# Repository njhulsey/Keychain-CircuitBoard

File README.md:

# Keychain-CircuitBoard
As a simple birthday present to my brother, I designed a simple circuit board that fits on your keychain and flashes when you shake it.

WHAT I LEARNED:
- Eagle design
- Vibration Sensor Switch
- OSH Park PCB Ordering

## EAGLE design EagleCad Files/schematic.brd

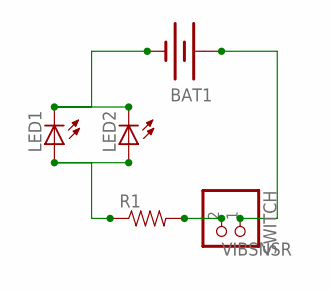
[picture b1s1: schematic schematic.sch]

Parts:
BAT1: BATTERY12PTH; BATTCON_12MM_PTH
LED1, LED2: LED5MM
R1: RESISTORKIT; AXIAL-0.3-KIT
SWITCH: PINHD-1X2; 1X02

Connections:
unnamed: BAT1.GND (-), LED1.K (C), LED2.K (C)
unnamed: LED1.A, LED2.A, R1.P$1 (1)
unnamed: R1.P$2 (2), SWITCH.2
VIBSNSR: BAT1.VCC@1 (+), SWITCH.1

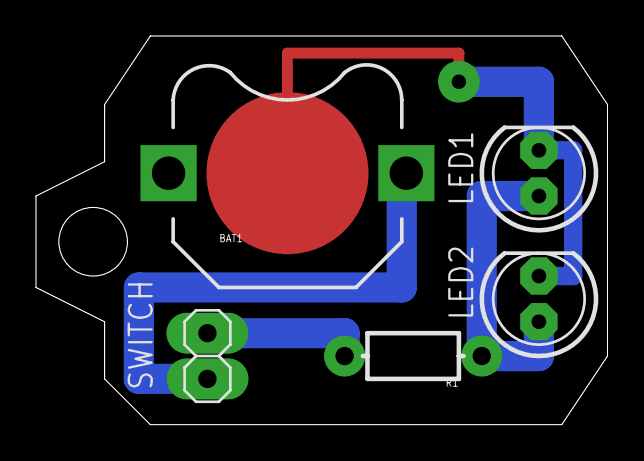
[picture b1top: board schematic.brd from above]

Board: 2 copper layers, 31.8 x 21.6 mm, 5 parts (0 on the bottom side), 4 nets.

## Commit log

2018-03-11 Create init

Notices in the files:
parts and their libraries:
SparkFun-Passives: Licensing: Creative Commons ShareAlike 4.0 International - https://creativecommons.org/licenses/by-sa/4.0
